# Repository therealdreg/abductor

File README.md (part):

# Abductor

The Abductor is an adapter board that lets you run CW312 targets on a ChipWhisperer CW308 UFO. The UFO
takes targets on three 20-pin 2.54 mm headers, and CW312 targets have a 1.00 mm card edge. The Abductor
has the UFO header footprint and a card-edge socket, and maps every UFO target signal to the CW312 edge.
Ten edge pins have no UFO counterpart and stay unconnected: TRACECLK and TRACED0-3, nRST_OUT, VCC1.0,
VCCADJ, CLKIN_n and CLKOUT_n. A CW312 target with the standard pinout should run on the UFO unless it
needs one of those. The name fits the UFO theme: the UFO abducts the CW312 target.

A dedicated target board built for one use case is usually the better choice. When that is not practical
or not possible, the Abductor is a low-cost alternative.

There are two variants. The straight board has a vertical socket on top and needs two small corners
trimmed off each CW312 target. The right-angle board has a right-angle socket on the underside, past the
end of the UFO headers, so no target needs trimming.

In my tests with three CW312 targets and a Husky Plus, both boards matched the target plugged directly
into a CW313 baseboard ("the CW313") on every chip and debug-port ID, known-answer test, key recovery and
fault outcome. Some single-run metrics were lower through the Abductor and some higher. SAM4S SNR was
11.5 dB through the Abductor and 12.2 dB on the CW313. K82F TVLA (a fixed-vs-random leakage t-test)
reached max |t| 100.6 on the straight board and 96.0 on the right-angle board, against 65.8 on the CW313,
whose capture was noisier.

Discussion and questions:
[NewAE forum thread](https://forum.newae.com/t/abductor-a-cw312-to-cw308-ufo-adapter-board/6514).

## Quick start

1. Order the boards from [prj/gerber.zip](prj/gerber.zip) (straight) or
   [prj/right_angle/gerber.zip](prj/right_angle/gerber.zip) (right-angle);
   [Ordering the PCB](#ordering-the-pcb) has the JLCPCB settings.
2. Solder one Samtec socket and three 20-pin male headers on each board
   ([Bill of materials](#bill-of-materials)).
3. For the straight board, trim two corners off each CW312 target
   ([Trimming targets for the straight board](#trimming-targets-for-the-straight-board)).
4. Plug the Abductor into the UFO and connect the Husky Plus: the 20-pin ribbon, and Measurement Pos to
   the UFO's J17 SMA, with Crowbar on a tee for glitching ([Cables](#cables)).
5. Set the UFO jumpers and switches, and add the J8 wires for SWD or JTAG
   ([UFO jumpers and switches](#ufo-jumpers-and-switches), [Debug wires on J8](#debug-wires-on-j8)).
6. Install the Python packages, change the hard-coded paths in the scripts and run them
   ([Running the scripts](#running-the-scripts)).

## Scope and limitations

All results come from one operator on one bench, with one unit of each Abductor variant, one
ChipWhisperer Husky Plus and one of each target (CW312T-SAM4S, CW312T-iCE40UP, CW312T-K82F), at
chipwhisperer commit `3c8e4347`. Most figures (SNR, TVLA t, |rho|, glitch bypass rates) come from a
single run, and unless repeats are reported I did not measure their run-to-run or re-assembly variance.
Words like "same" and "close" describe these sessions, not the hardware in general. Numbers with a plot
or an evidence file in `validation/` can be checked against it. The rest come from script console output
that is not in the repository, such as the K82F CPA, noise and mask figures, the glitch rates and the Lab
2_1B margins.

I am an enthusiast, not a professional hardware or side-channel engineer. The board and these notes may
contain mistakes or design choices a specialist would make differently. Read them as an informal
engineering log written in good faith, not as a datasheet or a qualified test report. After this testing
I consider the electrical design validated for my own use. Corrections and reviews are welcome.

## Building the board

### Ordering the PCB

Gerbers: [prj/gerber.zip](prj/gerber.zip) for the straight board and
[prj/right_angle/gerber.zip](prj/right_angle/gerber.zip) for the right-angle board. I do not work in
KiCad regularly, so review the sources and the gerbers before you order boards or rely on them.

The board carries many signals: power and shunt sensing, the HS2 clock (the ChipWhisperer high-speed
clock output), serial, the crowbar glitch path, the JTAG and SWD lines, the trigger, the LEDs and GPIO. I
chose six layers to route them comfortably. Every signal and rail runs as a 0.2 mm track on the four
inner layers. The two outer layers are ground pours, and ground fills the inner layers around the tracks.
At about 7 MHz the signal-integrity gain should be small, and my results show no consistent improvement
over a target plugged directly into the CW313. I never built a four-layer board, so I cannot say whether
it would perform the same.

The finish is ENIG. Both Samtec sockets are through-hole parts and the board has no gold-finger edge of
its own, so a cheaper HASL finish would most likely work too.

I ordered five of each variant from JLCPCB (https://jlcpcb.com/quote). It was a small, cheap order, and
the boards worked in all my tests. JLCPCB made them to this spec:

| JLCPCB parameter | Value |
|---|---|
| Base material | FR-4, TG135 |
| Layers | 6 |
| Dimensions | 54 mm × 67 mm (straight), 54 mm × 84.5 mm (right-angle) |
| Thickness | 1.6 mm |
| Outer / inner copper | 1 oz / 0.5 oz |
| Surface finish | ENIG, 1 µin gold (1U″) |
| Solder mask / silkscreen | Green / white, ink-jet |
| Via covering | Epoxy filled and capped |
| Min via | JLCPCB option: 0.3 mm hole, 0.4 to 0.45 mm diameter. The vias on both boards are 0.3 mm hole, 0.6 mm diameter |
| Electrical test | Flying-probe, full |
| Appearance quality | IPC Class 2 |
| Outline tolerance | ±0.2 mm |

### Bill of materials

| Part | Description | Link |
|---|---|---|
| Samtec PCIE-064-02-F-D-TH | Card-edge socket for the straight board: 1.00 mm pitch, 64 positions (the length of a PCIe x4 slot), through-hole | [Mouser](https://www.mouser.es/ProductDetail/Samtec/PCIE-064-02-F-D-TH?qs=iT52DjcXudu3X3%2FATBSy9g%3D%3D) |
| Samtec PCIE-064-02-F-D-RA | Right-angle version of the same socket, for the right-angle board | [Mouser](https://www.mouser.es/ProductDetail/Samtec/PCIE-064-02-F-D-RA?qs=92ilVni64gwDtfpZKan9%2FQ%3D%3D) |
| Preci-dip 800-10-020-10-001101 | Male header: 20-pin, 2.54 mm machined pin strip | [Mouser](https://www.mouser.es/ProductDetail/437-8001002010001101) |
| Preci-dip 801-87-020-10-001101 | Female socket strip: 20-pin, 2.54 mm machined, the header used on the CW308 itself. Not fitted on my boards; NewAE suggests it for sockets on its own CW308 to CW312 adapter | [Mouser](https://www.mouser.es/ProductDetail/437-8018702010001101) |

Each board takes one Samtec socket and three 20-pin male headers. The headers sit on the back of the
board, with their pins pointing down into the UFO. The PCB has no other parts: the Abductor only routes
signals.

NewAE's CW313 documentation only calls its socket the "cost-optimized CW312 card edge connector". The
CW313's Altium source in
[newaetech/chipwhisperer-target-cw313](https://github.com/newaetech/chipwhisperer-target-cw313) lists it
as a Samtec PCIE-064-02-S-D-RA. I picked the two Samtec sockets from the same PCIE series; NewAE does not
specify them. I use them only for their mechanical fit to the 1.00 mm card edge. Their PCIe signaling
rating does not matter here, since nothing on the edge comes near PCIe rates: DC rails, a clock of about
7 MHz, and slow serial, debug and GPIO lines.

### Trimming targets for the straight board

**On the straight board you have to trim two small corners off each CW312 target board**, one on each
side of the card edge. They hit the Abductor's header pins when the target is seated. The straight
board's vertical socket sits inside the UFO header frame, and the official ChipWhisperer target boards
are fixed products, so the design cannot avoid the corners. You trim each target once.

The photos show the trim on a CW312T-K82F target. The first marks the two corners. Nip each corner with
flush cutters, away from the target's mounting hole, then sand the edge, as the next two show.

This is roughly how much of the corner to remove:

### KiCad 10 sources

The KiCad projects are in [prj/](prj/) for the straight board and [prj/right_angle/](prj/right_angle/)
for the right-angle board. The schematic comes from NewAE's `CW308T_toCW312T` design in
[newaetech/chipwhisperer-target-cw308t](https://github.com/newaetech/chipwhisperer-target-cw308t/tree/main/CW308T_toCW312T),
an Altium schematic with no PCB layout or gerbers. That design is NewAE's "CW308 to CW312 Adapter", which
goes the other way: a CW308-style target solders onto it, and its card edge plugs into a CW312 baseboard
such as the CW313. NewAE ships it in the Husky Plus kit. I did the PCB layout in KiCad. The design uses
[ViaStitching](https://github.com/dobredanielstelian/ViaStitching), a KiCad 10 port of JS Reynaud's
via-stitching plugin (`jsreynaud/kicad-action-scripts`), and uPesy's easyeda2kicad
(`pip install easyeda2kicad`), whose output targets KiCad 6 and later. I imported the two socket
footprints with easyeda2kicad. The first command is for the straight board and the second for the
right-angle board:

```
python -m easyeda2kicad --full --lcsc_id=C4597619 --output "C:\\path\\to\\project" --project-relative --overwrite

python -m easyeda2kicad --full --lcsc_id=C4571870 --output "C:\\path\\to\\project\\right_angle" --project-relative --overwrite
```

LCSC `C4597619` is the Samtec PCIE-064-02-F-D-TH and `C4571870` the Samtec PCIE-064-02-F-D-RA. The
imported footprints, symbols and 3D models are already in each project folder (`easyeda2kicad.pretty`,
`easyeda2kicad.kicad_sym` and `easyeda2kicad.3dshapes`), so you need these commands only to import them
again.

The schematic names the two clock nets from the scope side. Its `/CLKOUT` net carries HS2 to card-edge
pin B27, the target's CLKIN, and its `/CLKIN` net carries the target's clock output from edge A29 to the
UFO.

### Pin map

UFO pins A, B and C are NewAE's target headers J7 (west), J9 (south) and J11 (east). CW312 pins A and B
are the two sides of the card edge. Both boards map the pins the same way.

| Signal | UFO pin | CW312 edge pin |
|---|---|---|
| VCC1.2 | C11 | B7 |
| VCC1.8 | C12 | B8 |
| VCC2.5 | C13 | A4 |
| VCC3.3 | C14 | A5 |
| VCC5.0 | C15 | A6 |
| FILTIN | C8 | B5 |
| FILT_HP | C6 | B4 |
| FILT_LP | C5 | A3 |
| SHUNTH | C3 | B2 |
| SHUNTL | C2 | B1 |
| IOVREF (the UFO's VREF) | A20 | B10 |
| Clock to the target (UFO CLK-IN, net `/CLKOUT`) | A3 | B27 |
| Clock from the target (UFO CLKOUT, net `/CLKIN`) | A5 | A29 |
| GPIO1/TX | A7 | B16 |
| GPIO2/RX | A8 | B17 |
| GPIO3 | A9 | B18 |
| GPIO4/TRIG | A10 | B19 |
| nRST | A11 | B14 |
| SCK | A12 | B20 |
| MISO | A13 | B23 |
| MOSI | A14 | B24 |
| PDIC | A17 | B25 |
| PDID | A18 | B26 |
| JTAG_TRST | B2 | A32 |
| JTAG_TDI | B3 | B29 |
| JTAG_TDO | B4 | B30 |
| JTAG_TMS | B5 | B31 |
| JTAG_TCK | B6 | B32 |
| JTAG_VREF | B7 | A26 |
| JTAG_nRST | B8 | A31 |
| LED1 | C18 | B11 |
| LED2 | C19 | B12 |
| LED3 | C20 | B13 |
| HDR1 to HDR10 | B11 to B20 | A9 to A18 |
| GND | A2, A4, A6, A15, A16, B1, B9, B10, C1, C4, C7, C9, C10, C16, C17 | A1, A2, A8, A20, A27, A28, B3, B9, B15, B21, B22 |
| TRACECLK, TRACED0 to TRACED3 | not connected | A21, A22 to A25 |
| nRST_OUT | not connected | A19 |
| VCC1.0 | not connected | B6 |
| VCCADJ | not connected | A7 |
| CLKIN_n, CLKOUT_n | not connected | A30, B28 |
| UFO spare pins | A1, A19 | not connected |

## Using the board

Plug the Abductor into the UFO target headers like any CW308 target, then plug the CW312 target into the
Abductor's socket. The Abductor has no jumpers or settings. To pull it off the UFO without stressing or
damaging the PCB I use a 3D-printed removal tool:
https://github.com/therealdreg/removal_tool_cw308_ufo_chipwhisperer

The software needs no change for the Abductor. The same scripts in `validation/scripts/` and the same
target builds ran on the CW313 and on both boards: `PLATFORM=CW312_SAM4S` for the SAM4S, the
`iCE40UP5K_SS2` bitstream for the iCE40 and `PLATFORM=CW308_K82F` for the K82F.

### Cables

The Husky Plus connects to the UFO with two cables, as in the photo:

- The 20-pin ribbon, from the Husky Plus "20-Pin Connector" to the UFO's 20-pin header J1. It carries the
  HS2 clock, serial on TIO1 and TIO2, the trigger on TIO4, nRST, PDIC, the SPI lines and the 3.3 V that
  powers the UFO. NewAE rates that 3.3 V at 200 mA, and the 20-pin 5 V pin is connected only on a CW-Pro,
  so the UFO runs on 3.3 V alone.
- An SMA cable from "Measurement Pos" to J17, the UFO's only SMA (silkscreen VOUT). Its center pin is
  SHUNTL, the low side of the shunt resistor on the CW312 target. For voltage glitching, put an SMA tee
  on J17 and run a second cable from "Crowbar" to it. The tee that came with the UFO works;
  [Bypass rate by tee and setup](#bypass-rate-by-tee-and-setup) compares it with an Amphenol 132217.

"Measurement Neg", "Trig/Glitch" and "Aux" stay unused. For single-ended measurement NewAE recommends
fitting the short-circuit cap that ships with the Husky on Measurement Neg, which makes the trace
slightly less noisy; my bench ran without it. On the CW313 the two SMAs are wired together, so Crowbar
and Measurement Pos take one each and need no tee.

### UFO jumpers and switches

These settings run all three targets from the Husky Plus alone, with nothing on the UFO's DC jack. The
bench photos show the J3, J4 and J14 caps fitted and J16 open, but the regulator switches are too small
to read in them, so the switch settings below follow from what the targets need.

| Jumper or switch | Setting | Why |
|---|---|---|
| J3, clock | HS2/OUT to CLKIN, the NewAE default | sends the Husky Plus HS2 clock to the target CLKIN. The other positions take the X1 crystal or send CLKFB, the target's clock output, to the ChipWhisperer |
| 3.3V SRC switch | J1/CW | takes 3.3 V straight from the 20-pin cable. The LDO position needs a DC supply or the CW-Pro 5 V |
| 1.2V LDO SRC switch | J1 | feeds the 1.2 V LDO from the ChipWhisperer 3.3 V. The SAM4S and the iCE40 take their 1.2 V core supply from it; the K82F (revision -03, the board used here) runs on 3.3 V only |
| J14, filter input | FILT, the NewAE default | the target feeds its core supply into the UFO filter through FILTIN (CW312 edge B5). The VADJ position feeds the filter from the adjustable LDO instead: set its voltage first, because the SAM4S and iCE40 cores run at 1.2 V |
| J16, shunt | open | a cap across SH- and SH+ shorts the shunt and removes the power signal. A cap across GND and SH- shorts the target supply to ground through the shunt: on the K82F that is about 330 mA from the Husky Plus 3.3 V, which is rated at 200 mA |
| J4, VREF | J5-VREF (the NewAE default) or CW 3.3 V | sets the clamp level of the 20-pin I/O lines. J5-VREF takes it from the target's VREF pin, which the Abductor carries to CW312 edge B10 (IOVREF), and all three targets drive that pin at 3.3 V. CW 3.3 V sets the same 3.3 V from the 20-pin cable. The close-ups with the K82F appear to show the cap on the CW 3.3 V side |
| EXT-DC switch | either | matters only with a DC supply on the jack |

These targets use none of the other supplies, so the 1.8V, 2.5V and 3.3V LDO SRC switches, the 5V SRC
switch, the VADJ SRC switch and the VADJ trimmer can stay as they are.

On the CW313, JP2 stays on target GPIO4 (the default) for the trigger, and the JP3 caps make the debug
bridge described in [SWD and JTAG debug](#swd-and-jtag-debug).

### Debug wires on J8

The UFO has no JP3 jumpers like the CW313's, so SWD and JTAG on the SAM4S, and flashing the K82F, need
jumper wires on the UFO from J5, the pin header next to J4 that carries the target connector's
ChipWhisperer signals, to the JTAG pins of J8. J8 is printed, from the left: GND, J_TRST, J_TDI, J_TDO,
J_TMS, J_TCK, J_VREF, nRST, GND, GND, then H1 to H10. The silkscreen font draws a V like a U, so J_VREF
can read as J_UREF (and VREF on J5 as UREF). Ground is already common through the 20-pin ribbon. SWD
needs wires 1 to 3, and full JTAG adds 5 and 6:

| Wire | From | To (J8) | Role |
|---|---|---|---|
| 1 | `SCK` | `J_TCK` | SWCLK |
| 2 | `PDID/CS` | `J_TMS` | SWDIO |
| 3 | `VREF` | `J_VREF` | JTAG_VREF for the pull-ups |
| 4 | `nRST` | `J_TRST` (SWD, K82F) or `nRST` (JTAG) | optional; OpenOCD drives no reset |
| 5 | `MOSI` | `J_TDI` | TDI, full JTAG only |
| 6 | `MISO` | `J_TDO` | TDO, full JTAG only |

SWD needs wire 3: without it OpenOCD failed with `cannot read IDR` in my setup. Wire 4 is optional, and
the logs show it on two different pins. The SWD and K82F sessions ran it to J_TRST, which reaches JTAG
TRST at CW312 edge A32 (unconnected on the SAM4S and the iCE40, PTA5/TRST on the K82F). The JTAG session
ran it to J8's nRST, which reaches edge A31 (JTAG_nRST, which the SAM4S ties to its nRST). OpenOCD drove
no reset line in any session. Take all these wires off before you use the iCE40. They tie `nRST`, `VREF`
and the SPI lines to the `J8` JTAG pins, and in my tests the iCE40's SS2 serial only worked without them.

## Validation

I tested the board on ChipWhisperer hardware one demo at a time, in the course order starting with
`sca101`, and checked each result before moving on. The tests check that the Abductor carries the signals
each demo needs and gives valid side-channel data.

The tests ran on three setups with the same targets and Husky Plus: the straight board, the right-angle
board, and the CW313, where the target plugs directly into the CW313 baseboard with no UFO and no
adapter. Results are from the straight board unless a section says otherwise. In file names and script
labels, `abductor` means the straight board.

The right-angle board's socket is a right-angle part, so its traces are a little longer and routed
differently. That could add series inductance and loop area on the crowbar/VOUT and shunt paths, or
slightly reduce the measurement bandwidth. I re-ran all three targets through it with the same Husky
Plus, UFO and scripts, one test at a time, and reconnected the Husky Plus USB between tests. A test that
failed on the first attempt was re-run after a USB reconnect.

### Results

In the verdict column, identical means a bit-exact match of a fixed value (IDs, known-answer tests). Same
means the same outcome or count. Close means a difference these runs cannot resolve, so a small effect is
neither shown nor ruled out. Glitch points are (width, offset, ext_offset): width and offset are in Husky
phase-shift steps, and ext_offset is in target clock cycles after the trigger.

| Test | Metric | Straight | Right-angle | CW313 | Verdict |
|---|---|---|---|---|---|
| Bring-up | traces, serial echoes | 10/10, 10/10 | 10/10, 10/10 | 10/10, 10/10 | same |
| Bring-up | mean trace peak-to-peak (normalized ADC units) | 0.57 | 0.68 | 0.62 | within 19%, one run each |
| CPA (AES) | full key | yes | yes | yes | same |
| CPA | traces to rank 0 (all 16 key bytes ranked first) | 30 | 30 | 30 | same |
| DPA (AES) | full 16-byte key | yes | yes | yes | same |
| Password SPA | recovered | `h0px3` | `h0px3` | `h0px3` | same |
| Password SPA | winner margin | 22x to 24x | 23x to 25x | 23x to 24x | close |
| SNR | peak, 1500 traces | 14.1 (11.5 dB) | 14.0 (11.5 dB) | 16.7 (12.2 dB) | CW313 18% higher (linear) |
| TVLA | max \|t\| (3000 traces, threshold 4.5) | 60.7 | 59.5 | 60.7 | close |
| GPIO3 | TIO3 toggles | yes | yes | yes | same |
| SWD | DPIDR, chip ID | `0x2ba01477`, `0x288b07e1` | `0x2ba01477`, `0x288b07e1` | `0x2ba01477`, `0x288b07e1` | identical |
| JTAG | TAP IDCODE | `0x4ba00477` | `0x4ba00477` | `0x4ba00477` | identical |
| Voltage glitch, high-power | best cell found (width, offset, ext_offset) | (1950, 2480, 129) | (2000, 2450, 129) | (1950, 2460, 129) | same ext_offset, offsets 2450 to 2480 |
| Voltage glitch, high-power | batch bypass rate (200 attempts) | 49.5% | not measured | 40.5% | gap not resolved (p about 0.07) |
| Voltage glitch, high-power | peak bypass rate (40 attempts at the best cell) | 78% and 98% (Amphenol tee), 55% (stock tee) | 90% (36/40) | 85% (34/40) | bypasses on all three; single runs do not rank them |
| Voltage glitch, low-power | crashes at repeat 1, 2, 4, 8 | none at 1, all at 2 to 8 | none at 1, all at 2 to 8 | none at 1, all at 2 to 8 | same threshold |
| Clock glitch | faults the SAM4S | yes | yes | yes | same |
| LED1, LED2, LED3 | blink in sequence | yes | yes | yes | same |
| Memory dump | crowbar on the send loop | 510 bytes at (2000, 2480, 2122), no secret | 510 bytes at (1900, 2200, 88), contains the secret | 510 bytes at (2000, 2480, 2122) | same fault and length; the right-angle glitch point differs |
| iCE40 AES | known answer `AES(0,0)` | `66e94bd4...` | `66e94bd4...` | `66e94bd4...` | identical |
| iCE40 CPA | traces to full key (grid ..., 2000, 3000) | 3000 | 3000 (repeat; first run 5000) | 3000 | same |
| iCE40 TVLA | max \|t\| (4000 traces, threshold 4.5) | 85.0 | 85.8 | 89.3 | within 5% |
| iCE40 DFA (differential fault attack) | full key (phoenixAES, round-8 and round-9 faults) | 16/16 | 16/16 | 16/16 | same |
| K82F AES | known answer `AES(2b7e..,00..0f)` | `50fe67cc...` | `50fe67cc...` | `50fe67cc...` | identical |
| K82F TVLA | max \|t\| (8000 traces, threshold 4.5) | 100.6 | 96.0 | 65.8 | all far above 4.5, wide spread |
| K82F CPA | byte-0 \|rho\| (50k traces; right-angle 30k) | 0.104 | 0.104 | 0.095 | close (standard error about 0.005 each) |
| K82F CPA | full AES key, disjoint-set attack | not recovered (1/16 at 50k, 0/16 at 30k) | not recovered (0/16 at 30k) | not recovered (0/16) | same; the limit is the target (one control run) |

Traces to rank 0 is a single-run count on a coarse trace grid. It depends on the data, can change from
run to run, and is not a guessing-entropy average (the mean rank of the correct key over many runs).

## CW312T-SAM4S

### Bring-up

All six steps of a smoke test passed, so the Abductor routes clock, power, serial, ERASE and nRST, and
the chain from the Husky Plus through the UFO and the Abductor to the SAM4S works. The test builds
`simpleserial-base`, flashes it over SAM-BA and captures traces. Steps 2 to 5 each exercise a different
path through the Abductor. Script: [`smoke_bringup.py`](validation/scripts/smoke_bringup.py).

| # | Step | Abductor path | Result |
|---|---|---|---|
| 0 | Connect to the Husky Plus | none (scope only) | `cwhuskyplus`, FW 1.2.0 |
| 1 | Build the SAM4S firmware | none (host build) | `simpleserial-base-CW312_SAM4S.hex`, ROM 2.17% of 128 KB |
| 2 | Flash over SAM-BA (ERASE=`pdic`, `nrst`) | control and reset lines | program and verify OK in 5.0 s |
| 3 | Bidirectional UART, echo of the `p` command | serial TX and RX | 10/10 echoes correct |
| 4 | Trigger and capture | trigger and sync | 10/10 traces, 5000 samples each |
| 5 | Clock and power measurement | HS2 clock, shunt and SMA | mean per-trace peak-to-peak 0.57 and global sample std 0.14 (normalized ADC units), clean clock cycles |

### Side channel (sca101)

Every lab I ran passed. The `sca101` course builds up from timing differences to a full AES key recovery.
I skipped Lab 3_2, which is software only, and Lab 4_1, a low-impact stepping stone. Labs 4_3, 5_1 and
6_4 are pending.

| Lab | Title | Firmware | Result |
|---|---|---|---|
| 2_1A | Instruction power differences | simpleserial-base | pass |
| 2_1B | Power analysis for password bypass | basic-passwdcheck | pass |
| 3_1 | Large Hamming weight swings | simpleserial-aes (TINYAES128C) | pass |
| 3_2 | Recovering data from a single bit | none | skipped (software only) |
| 3_3 | DPA on firmware implementation of AES | simpleserial-aes (TINYAES128C) | pass, full key |
| 4_1 | Power and Hamming weight relationship | simpleserial-aes | skipped |
| 4_2 | CPA on firmware implementation of AES | simpleserial-aes (TINYAES128C) | pass, full key in 30 traces |
| 4_3 | ChipWhisperer Analyzer CPA attack | simpleserial-aes | pending |
| 5_1 | ChipWhisperer CPA attacks in practice | simpleserial-aes | pending |
| 6_4 | Jittery triggering on UART | simpleserial-aes (TINYAES128C) | pending |

#### Lab 2_1A: instruction power differences

I inserted different instruction blocks between `trigger_high()` and `trigger_low()` in
`simpleserial-base`, then built (ChipWhisperer's default `-Os`), flashed and captured each one. As the
lab instructs, I removed the serial response (`simpleserial_put`) from `get_pt()`, so no reply follows
the block. The framework still sends its `z00` ack. `capture_trace` reads it in place of the missing `r`
packet, warns `Unexpected start to command` and keeps the trace. Serial stays in sync because
`simpleserial_write` flushes the receive buffer before each command. Script:
[`lab_2_1A.py`](validation/scripts/lab_2_1A.py).

The cost of each block is the trigger duration, `scope.adc.trig_count`. That counter counts ADC samples:
at `adc_mul=4` there are 4 samples per core clock cycle, so the counts are 4 times the core cycles.

| Instruction block | Trigger duration (ADC samples) | Cost against baseline |
|---|---|---|
| baseline (empty) | 492 | reference |
| 20x `A *= 2` (unrolled multiply) | 992 | +500, 25 ADC samples (6.25 core cycles) per volatile statement |
| loop x20 `A *= 2` (multiply) | 2132 | +1640, 82 ADC samples (20.5 core cycles) per iteration |
| loop x20 `A /= 3` (integer divide) | 2276 | +1784, 144 more than the multiply loop |

- The count was identical in all 15 captures of each block (min equals max), as expected from
  deterministic code clocked in step with the ADC. That is consistent with the count coming back through
  the Abductor uncorrupted. The right-angle board gave the same four counts.
- The unrolled block adds a flat cost per statement. The loop costs far more than the same 20 multiplies
  unrolled. That extra fits per-iteration loop overhead (the volatile counter load and store, compare and
  branch), but the measurement only records the total.
- The divide loop costs more than the multiply loop. `A` is a `volatile long int`, so `A /= 3` is integer
  division. The compiler can emit the multi-cycle Cortex-M4 `SDIV` or, for a constant divisor like 3, a
  multiply-and-shift sequence, and the repository has no listing to tell which. The trigger duration
  cannot tell the two apart either, so it does not prove an `SDIV` ran.

Both figures label the counts as cycles and draw the block end at four times the count. The counts are
ADC samples, so the blocks end at samples 492, 992, 2132 and 2276, and `lab_2_1A.py` labels and draws
them that way.

#### Lab 2_1B: power analysis for password bypass

The power traces recover the password of `basic-passwdcheck`, `h0px3`, which matches the firmware
constant. The correct character wins every position by 22x to 24x. The firmware checks the password one
character at a time and stops at the first wrong one. Each correct character runs one more loop
iteration, so the trace stays active longer before it diverges. The attack captures one trace per
candidate character, scores it against a wrong-character reference with the sum of absolute differences
(SAD), keeps the best score, and moves to the next position with the known prefix. Script:
[`lab_2_1B.py`](validation/scripts/lab_2_1B.py).

| Position | Recovered char | SAD (winner) | SAD (2nd best) | Margin |
|---|---|---|---|---|
| 0 | `h` | 286.6 | 11.9 | 24.0x |
| 1 | `0` | 284.6 | 12.4 | 22.9x |
| 2 | `p` | 280.3 | 12.7 | 22.1x |
| 3 | `x` | 274.5 | 12.4 | 22.1x |
| 4 | `3` | 301.7 | 12.3 | 24.4x |

Margins come from the full-precision SAD values, so they can differ slightly from dividing the rounded
columns. In the divergence plot the correct and wrong first-character traces overlap until the compared
byte and split around sample 430.

#### Lab 3_1: large Hamming weight swings

The target's power depends on the data it handles as well as on the code path. With `simpleserial-aes`
(TINYAES128C) and a fixed key, I captured 200 traces with plaintext byte 0 forced to `0x00` (Hamming
weight 0) or `0xFF` (Hamming weight 8). Bit 0 of the original random byte picks the value (odd gives
`0xFF`, even gives `0x00`), which splits the traces about evenly. The difference of the two group means
is the data-dependent leak. Script: [`lab_3_1.py`](validation/scripts/lab_3_1.py).

| Metric | Value |
|---|---|
| Traces | 200, about 100 at `0x00` and 100 at `0xFF` |
| Peak difference | 0.0254 in magnitude at sample 528 (negative) |
| Off-peak std (difference trace beyond ±400 samples from the peak) | 0.0008 |
| Leak-to-noise ratio | peak about 32x the off-peak std (an informal single-run ratio, not an SNR) |

A sharp negative spike at sample 528, where the target loads and processes that byte, dominates the
difference of means. The spike is negative because ChipWhisperer measures across a shunt: more power
reads as lower voltage, and `0xFF` (more bits set) draws more power than `0x00`. A smaller positive
spike, about +0.013 near sample 1930, lines up with the S-box output of the same byte. The Lab 3_3 DPA
peak sits at the same sample. The sign fits too, because `SBox(0xFF XOR 0x2b) = 0x48` has fewer bits set
than `SBox(0x00 XOR 0x2b) = 0xf1`. CPA on AES exploits that S-box leak, `HW(SBox(pt XOR key))`.

On the right-angle board the leak sits at the same sample 528, with a peak difference of 0.019 and a
leak-to-noise ratio of about 27x.

#### Lab 3_3: DPA on firmware implementation of AES

Single-bit DPA recovers the known key, `2b7e151628aed2a6abf7158809cf4f3c`, in all 16 bytes. This is the
first full key recovery in the suite. With `simpleserial-aes` (TINYAES128C) and a fixed key, I captured
2500 traces with random plaintexts, at about 119 traces/s. For each key byte and each of the 256 guesses,
the script splits the traces by bit 0 of `SBox(plaintext_byte XOR key_guess)` and subtracts the two group
means. The guess with the highest peak is the key byte. Script:
[`lab_3_3.py`](validation/scripts/lab_3_3.py).

For every byte the correct guess peaks above the best wrong guess. For byte 0 the correct guess `0x2b`
peaks sharply near sample 1930, at about 0.0033. The strongest wrong guesses reach about 0.0025 (`0x99`,
elsewhere in the trace) and about 0.002 (`0x40`, a ghost peak at the same sample). The margin is modest
because single-bit DPA is noisier than CPA.

#### Lab 4_2: CPA on firmware implementation of AES

Correlation power analysis (CPA) recovers the same key, all 16 bytes, from the first 30 traces on all
three setups. It is the stronger attack here, since it is less noisy than single-bit DPA. The model is
`HW(SBox(plaintext_byte XOR key_guess))`, and for each key byte the guess whose model has the highest
absolute Pearson correlation with the traces (max |rho| over the samples) is the key byte. Script:
[`lab_4_2.py`](validation/scripts/lab_4_2.py).

- 1000 traces captured, at about 120 traces/s.
- The correct byte reaches |rho| 0.91 to 0.94 and the best wrong guess 0.20 to 0.31, so the correct byte
  leads by 0.6 to 0.7. The correct byte reaches 0.87 to 0.90 on the right-angle board and 0.89 to 0.91 on
  the CW313.
- 30 traces is the first point on the trace grid (..., 20, 30, 40, ...) where all 16 key bytes reach rank
  0.

### SNR and TVLA

Two standard leakage metrics show how cleanly each path captures the AES leak. Script:
[`signal_integrity.py`](validation/scripts/signal_integrity.py), with a 3000-sample window on
`simpleserial-aes`. I ran it on all three setups at the same trace counts, so that only the path differs.

| Path | SNR peak, linear (dB) | TVLA max \|t\| |
|---|---|---|
| Straight board | 14.1 (11.5 dB) | 60.7 |
| Right-angle board | 14.0 (11.5 dB) | 59.5 |
| CW313 | 16.7 (12.2 dB) | 60.7 |

- SNR is `calculate_snr` from `chipwhisperer.analyzer`, with the Hamming weight of the S-box (SubBytes)
  output for byte 0 over 1500 random-plaintext traces, at the leak sample. ChipWhisperer's
  `calculate_snr(db=True)` returns `20*np.log(snr)`, and `numpy.log` is the natural log, so it reports
  `20*ln(snr)`, which is not standard dB. The dB values here are `10*log10` of the linear SNR (see
  `software/chipwhisperer/analyzer/attacks/snr.py`).
- TVLA is a non-specific fixed-vs-random Welch t-test, the leakage-detection method of Goodwill, Jun,
  Jaffe and Rohatgi (2011), later branded TVLA. It runs over about 1500 fixed and 1500 random traces
  (3000 total, split by a coin flip per trace), and the usual detection threshold is 4.5. A raw t value
  also grows with the trace count, so it is only a relative measure at matched counts.

The exact TVLA match between the straight board and the CW313, to three significant figures from two
independent trace sets, is chance and will not repeat to that precision. SNR is about 0.7 dB higher on
the CW313. With one estimate per path there is no spread to test that against, so a small real loss
through the Abductor is neither shown nor ruled out. The same holds for the somewhat smaller Lab 3_1 and
Lab 4_2 leaks on the right-angle board. Settling it would need repeated captures on each path.

SNR and TVLA come from the ChipWhisperer capture path, not from a direct bench measurement of the board.
I may later probe both boards directly with my MHO98 and an LD-ASP-2.7 single-ended active probe.

### Fault injection (fault101)

The glitch tests used the SMA tee from [Using the board](#using-the-board), stock UFO jumpers and the
stock SMA cables that ship with the Husky Plus and the CW313. The Husky Plus has a high-power and a
low-power crowbar MOSFET, and each one briefly shorts the target supply. This exercises the Abductor's
crowbar path, a different use of the power pins from power measurement.

#### Fault 2_2: voltage glitching to bypass password

`simpleserial-glitch` checks a fixed password (`touch`). A wrong password (`[0]*5`) normally returns
`passok=0`. A high-power crowbar glitch during the compare loop can leave `passok=1`, so the firmware
accepts the wrong password. That is a bypass. I used `scope.vglitch_setup('hp')`, with
`scope.io.vglitch_reset()` after each attempt, and swept widths 1900 to 2200, offsets 2380 to 2500 and
ext_offset 122 to 140, twice each: 2964 attempts. Bypasses appeared only at ext_offset 129, on both
boards:

| Board | Bypasses | Offsets | Widths |
|---|---|---|---|
| Straight | 12 in 2964 | 2460 to 2500 | 1900 to 2140 |
| Right-angle | 15 in 2964 | 2430 to 2500 | 1960 to 2200 |

Both windows reach the edge of the swept grid, so they may extend further. On the straight board the 12
bypasses are 0.4% of the whole grid, and 20% of the 60 attempts at offsets 2460 to 2500 and ext_offset
129 over all six widths. The window is a single ext_offset value, so a sweep with a coarse ext_offset
step misses it. [`fault_2_2_vglitch_find.py`](validation/scripts/fault_2_2_vglitch_find.py) finds the
first bypass with a sweep that is coarse in width and offset but steps ext_offset by 1, and
[`fault_2_2_vglitch_bypass.py`](validation/scripts/fault_2_2_vglitch_bypass.py) maps the window. The
shared VOUT tee and the SMA cabling may also narrow the window; I did not measure that.

#### Bypass rate by tee and setup

In these tests the Abductor carried voltage glitching with either tee. I measure the peak bypass rate at
each setup's best cell: a fine search finds the cell, then 40 attempts run there. The best cell is the
best on the swept grid, not a verified global optimum.
[`vglitch_peakrate.py`](validation/scripts/vglitch_peakrate.py) runs this on a fixed grid (widths 1800 to
2200, offsets 2360 to 2520, ext_offset 128 to 130) and warns when the best cell sits on a width or offset
edge, where the rate comes out low.

| Setup | VOUT tee | Peak bypass rate |
|---|---|---|
| Straight board, back to back on one fresh re-assembly | Amphenol 132217 (low-cost SMA jack-plug-jack T, Mouser 523-132217) | 31/40 = 78% |
| Straight board, the same re-assembly | the tee that came with the UFO | 22/40 = 55% |
| Straight board, another re-assembly | Amphenol 132217 | 39/40 = 98% |
| CW313 | none (two dedicated SMAs) | 34/40 = 85% |

The right-angle board gave 36/40 = 90% at its best cell (95% CI about 76% to 97%), which overlaps the
straight board's 78% to 98% with the Amphenol tee.

The batch rate over 200 attempts (five 40-attempt batches,
[`vglitch_rate_robust.py`](validation/scripts/vglitch_rate_robust.py)) at each setup's best cell, found
the same day, is 49.5% through the straight board and 40.5% on the CW313. The 9-point gap is about 1.8
standard errors (standard error of the difference about 5 points, two-sided p about 0.07), so 200
attempts per setup cannot resolve it. These batch rates sit below the 40-attempt peaks:
`vglitch_rate_robust.py` picks its cell with a coarser search (2 attempts per cell, offset step 20), and
the peaks came from other assemblies.

With the Amphenol tee the Abductor is not measurably worse than the CW313: 31/40 and 39/40 against 34/40,
two-sided Fisher exact p 0.57 and 0.11. The stock-tee run (22/40) is lower than the CW313's 34/40 (p
about 0.007), but I measured them on different assemblies, and re-assembly moved the Amphenol rate from
31/40 to 39/40 (p about 0.014). So these single runs do not rank the setups.

The Amphenol tee may help, but that is not established. A two-sided Fisher exact test on the back-to-back
counts (31/40 against 22/40) gives p about 0.06, above the 0.05 level, so one pair of 40-attempt runs
cannot settle it. The 22.5-point gap is about the size of the 20-point spread between the two Amphenol
re-assemblies. Pinning down a modest tee effect would take repeated swap-and-measure runs.

#### Low-power crowbar

[`fault_2_2_vglitch_lp.py`](validation/scripts/fault_2_2_vglitch_lp.py) uses the low-power crowbar
(`scope.vglitch_setup('lp')`) at width 2000, offsets 2440 to 2470 and ext_offset 126 to 136, and sweeps
`scope.glitch.repeat` over 1, 2, 4 and 8, with 18 attempts each. At repeat 1 there were no crashes (0 of
18, too few to rule out a low rate). At repeat 2, 4 and 8 the crowbar crashed the SAM4S on every attempt.
The sharp threshold indicates that the crashes follow the glitch setting instead of happening at random.
The right-angle board and the CW313 showed the same threshold. Both crowbars drive the same CROWBAR SMA,
so this test exercises the same SMA and VOUT path as the high-power one, not the `FILT_LP` pin.

#### Fault 2_3: voltage glitching to memory dump

`bootloader-glitch` answers a command with an 8-byte ack, sending exactly `ascii_idx` bytes with
`for(i=0; i<ascii_idx; i++) putch(ascii_buffer[i])`. A crowbar glitch on that loop bound makes the target
keep sending past the ack and dump the adjacent buffer and RAM, which can include the decrypted
`data_buffer`. Script: [`fault_2_3_memory_dump.py`](validation/scripts/fault_2_3_memory_dump.py), with
[`fault_2_3_baseline.py`](validation/scripts/fault_2_3_baseline.py) to confirm the protocol and measure
the send-loop `trig_count`. Both scripts sample at one ADC sample per target clock, so `trig_count` and
ext_offset are both in target clock cycles.

- The glitch is a high-power crowbar pulse at width 2000, offset 2480 and ext_offset 2122, inside the
  send loop (`trig_count` 2159). It lands 37 cycles before the loop ends, near the final bound check.
- The 8-byte ack became a 510-byte dump with the leftover input buffer and a block of binary RAM. The
  success marker `767` that the attack looks for is at offset 0x2a, inside the leftover input, which is
  the encrypted command text. So the marker shows an overrun, and this dump does not contain the
  decrypted secret.
- The hexdump in [`fault_2_3_memory_dump.txt`](validation/evidence/fault_2_3_memory_dump.txt) shows 601
  bytes because the printed text was saved as UTF-8: each byte from 0xa1 to 0xff except 0xad takes two
  bytes there (91 `c2`/`c3` pairs).
- Success is rare. The first one came after about 2100 swept attempts. That is the position of one
  success in an ordered parameter sweep, not a per-attempt hit rate, so take it as an order of magnitude.
  The glitch has to break the loop bound in a narrow window.
- All three dumps are 510 bytes. The CW313's came at the same glitch point, with its first success also
  near 2100 swept attempts. The right-angle board's came at (1900, 2200, 88), much later in the sweep, at
  attempt 13049. That fits a rare fault with several valid glitch points, and shows that an early glitch
  can work too. It is the only dump in the repository that contains the decrypted secret,
  `Don't forget to buy milk!`
  ([`fault_2_3_memory_dump_ra.txt`](validation/evidence/fault_2_3_memory_dump_ra.txt)).

#### Fault 1_2: clock glitching to bypass password

In ChipWhisperer's stock configuration the CW312T-SAM4S core runs directly on the external HS2 clock. The
SAM4S HAL switches the master clock to MAINCK in bypass mode (about 7.37 MHz, prescaler 1) and keeps the
PLLA out of the core path: `firmware/mcu/hal/sam4s/sam4s_hal.c` calls `osc_enable(OSC_MAINCK_BYPASS)` and
then `pmc_switch_mck_to_mainck(SYSCLK_PRES_1)`. So a glitch on HS2 reaches the core clock tree (MCK/HCLK)
with no PLL to regenerate the clock. The capture clock runs in step with the 7.363636 MHz HS2 clock,
which agrees with this but does not by itself rule out a PLL. The proof is the HAL source, and the fact
that clock glitches fault the core.

On PLL-clocked systems the PLL strongly attenuates a single external clock glitch, so a naive
single-cycle glitch usually fails. Faults there come from disturbing the PLL itself, for example driving
it into a transient frequency overshoot by manipulating its reference clock. See Selmke, Hauschild and
Obermaier, "Peak Clock: Fault Injection into PLL-Based Systems via Clock Manipulation", ASHES@CCS 2019,
Fraunhofer AISEC / ACM, DOI 10.1145/3338508.3359577.

On the CW313 I swept at repeat 1 only: widths 3350 to 3600, six offsets from 2300 to 2900 and ext_offset
85 to 158, about 5300 attempts. The clock glitch crashes the SAM4S, more often as the width grows. One
clean bypass appeared at the crash onset, at (3450, 2300, 142). It was a single event, so it gives no
success rate. On the map at width 3450, every crash and the bypass sit at offset 2300, the lowest offset
swept, spread across ext_offset 88 to 157; offsets 2400 to 2900 show nothing.

Through the straight board, a sweep over widths 3400 to 4500, offsets 2300 to 2900 and ext_offset 85 to
157 faults the SAM4S too. It runs 400 attempts at each value of `scope.glitch.repeat`, the number of
consecutive glitched cycles:

| Repeat | 1 | 2 | 4 | 8 | 16 | 32 |
|---|---|---|---|---|---|---|
| Crash rate | 2% | 15% | 20% | 30% | 34% | 42% |
| Clean bypasses | 0 | 0 | 1 | 1 | 1 | 0 |

The right-angle board showed the same pattern: the crash rate rose from about 2% at repeat 1 to about 40%
at repeat 32, with some clean bypasses. A higher repeat raises the crash rate; three clean bypasses are
too few to show whether it also raises the clean-fault rate.

A sweep that misses the reactive offsets or widths sees no effect at all, which looks like the path is
attenuating the glitch. At repeat 1 the straight board gave no clean bypass in 400 attempts and the CW313
gave one in about 5300, which does not separate the two paths. These single, unmatched runs cannot show
whether the path makes any difference; that would need matched sweeps on both setups.

Scripts: [`clock_glitch_cw313_bypass.py`](validation/scripts/clock_glitch_cw313_bypass.py) for the CW313
and [`clock_glitch_abductor_repeat.py`](validation/scripts/clock_glitch_abductor_repeat.py) for the
repeat sweep. The repeat sweep script prints its counts; no script in the repository draws the repeat
figure. [`clock_glitch_characterize.py`](validation/scripts/clock_glitch_characterize.py) maps glitch
width to effect, and
[`clock_glitch_cw313_isolation.py`](validation/scripts/clock_glitch_cw313_isolation.py) sweeps width,
offset and ext_offset on the CW313 to check whether the SAM4S rejects clock glitches.

### SWD and JTAG debug

SWD and full JTAG both work through the Abductor. The SAM4S gives the same DPIDR, core revision, TAP
IDCODE and chip ID through both boards as on the CW313. So the Abductor carries all four JTAG signal
lines: the data lines TDI and TDO and the control lines TMS and TCK. `JTAG_nRST`, `JTAG_TRST` and
`JTAG_VREF` were not exercised.

With the Husky Plus in MPSSE mode (its FTDI emulation) and OpenOCD, I took over the SAM4S via SWD: reset
and halt at the reset vector, then read the chip ID, SRAM, flash and core registers. The Husky Plus
drives SWD in non-DIO mode (`scope.enable_MPSSE(1)`), which puts the debug signals on the main 20-pin
SPI/PDI pins: PDID is SWDIO and SCK is SWCLK, the same mapping the non-Husky ChipWhisperer boards use.
OpenOCD then connects with `transport select swd` and the `at91sam4sXX` target config. In MPSSE mode the
USB PID stays `0xace6`, and the interface config is the stock ChipWhisperer `openocd/cw_openocd.cfg`.
Scripts: [`swd_debug.sh`](validation/scripts/swd_debug.sh) and
[`jtag_debug.sh`](validation/scripts/jtag_debug.sh).

I verified the flow on the CW313 first, to check the target and the toolchain. There the JP3 caps make
the bridge, so no external wiring is needed: `PDID` to `JTAG_TMS`, `SCK` to `JTAG_TCK`, `MOSI` to
`JTAG_TDI`, `MISO` to `JTAG_TDO`, `nRST` to `JTAG_nRST` and `PDIC` to `JTAG_TRST`. SWD needs the first
two, full JTAG the first four. Through the Abductor the bridge is the `J8` wires listed in
[Using the board](#using-the-board). From `J8` the debug lines reach the CPU through the UFO target
socket, the Abductor and the CW312 card edge.

The schematics do not explain why SWD needs the `VREF` wire. The UFO does not drive `JTAG_VREF` itself;
it only feeds the 100k pull-ups on the JTAG lines. The CW312T-SAM4S ties card-edge pin A26 (`JTAG_VREF`)
to its VCC, and the Abductor routes A26 to the UFO's `JTAG_VREF`. On the CW313, `JTAG_VREF` also comes
only from A26. The wire feeds the same net as the A26 route, so these sessions cannot tell the two apart.

OpenOCD drove no reset line. The raw CW313 logs print `none separate`, the reset configuration that
`cw_openocd.cfg` leaves (`reset_config srst_push_pull`), and the at91sam4 target config resets the core
with `cortex_m reset_config sysresetreq`. The same scripts and configs ran through the Abductor, so wire
4 was not exercised there either. `J_TRST` also lands, through the Abductor, on card-edge pin A32, which
the CW312T-SAM4S leaves unconnected.

The SWD readout through the straight board:

| Read over SWD | Value | Meaning |
|---|---|---|
| SWD DPIDR | `0x2ba01477` | ARM CoreSight SW-DP (DPv1) alive. This DPIDR is common on Cortex-M4 parts and later Cortex-M3 revisions, and identifies the debug port, not the core |
| Core | `Cortex-M4 r0p1` | SAM4S core, from CPUID |
| State | `halted due to debug-request` | the debugger halted the core straight out of reset, at the reset vector |
| CHIPID_CIDR @0x400E0740 | `0x288b07e1` | chip ID read from silicon, which decodes to ATSAM4S2A (Cortex-M4, 128 KB flash, 64 KB SRAM) |
| Flash @0x00400000 | SP `0x200011a8`, reset vector word `0x0040061d` | firmware vector table. Bit 0 of the reset entry marks Thumb state, so the handler is at `0x0040061c` |
| Registers | pc `0x0040061c`, sp `0x200011a8` | pc is the reset handler and sp the vector-table MSP, as expected after a reset halt |

The DPIDR, the CPUID core revision and the chip ID match the CW313 bit for bit, and the halt, flash and
register reads behave the same. The vector table, pc and sp depend on the firmware and differ from the
CW313 run only because I loaded a different build there. On the right-angle board the core halts at pc
`0x00400180` with sp `0x20001020`, and the SRAM and flash sections of that log are empty. So SWDIO (on
the TMS pin) and SWCLK (on the TCK pin) carry SWD end to end from the CW312 card edge to the UFO socket.

SWD leaves TDI and TDO unused. To exercise `JTAG_TDI` and `JTAG_TDO` I repeated the session in full JTAG
mode (`transport select jtag`) with wires 5 and 6 added. OpenOCD scanned the chain:

| Read over JTAG | Value | Meaning |
|---|---|---|
| TAP IDCODE | `0x4ba00477`, matches expected | ARM CoreSight JTAG-DP (`mfg: 0x23b (ARM Ltd), part: 0xba00, ver: 0x4`), captured in Capture-DR and shifted out on TDO |
| Core | `Cortex-M4 r0p1` | same core, from CPUID over JTAG |
| CHIPID_CIDR @0x400E0740 | `0x288b07e1` | chip ID, read over JTAG |

The IDCODE comes out on TDO, so it confirms `JTAG_TDO` (the MISO wire). The halt, chip ID, flash and pc
reads that follow shift their commands in on TDI and return data on TDO, so they also exercise `JTAG_TDI`
(the MOSI wire). The right-angle board gives the same IDCODE and reads. As expected, the TAP IDCODE
`0x4ba00477` differs from the SWD DPIDR `0x2ba01477`: they are the ID registers of the JTAG-DP and the
SW-DP, the two modes of the same CoreSight SWJ-DP debug port. Unlike the IEEE 1149.1 IDCODE, the SW-DP
DPIDR has a DP-version field in bits [15:12], and it encodes PARTNO in 8 bits against the IDCODE's 16.

Evidence: [`swd_cw313_dump.txt`](validation/evidence/swd_cw313_dump.txt),
[`swd_abductor_dump.txt`](validation/evidence/swd_abductor_dump.txt),
[`swd_abductor_ra_dump.txt`](validation/evidence/swd_abductor_ra_dump.txt),
[`jtag_cw313_dump.txt`](validation/evidence/jtag_cw313_dump.txt),
[`jtag_abductor_dump.txt`](validation/evidence/jtag_abductor_dump.txt) and
[`jtag_abductor_ra_dump.txt`](validation/evidence/jtag_abductor_ra_dump.txt). The straight-board SWD and
JTAG files are edited summaries of the OpenOCD output; the CW313 files are the raw logs.

### Signal coverage

Every pin the Abductor routes was exercised by a test, checked for continuity, or is marked as not
exercised in the matrix. The functional tests run small firmwares on the SAM4S.
[`signal_test.py`](validation/scripts/signal_test.py) flashes a test firmware and, for GPIO3, reads TIO3
back on the Husky Plus; the LED check is visual. The firmware sources are
[`led-blink/`](validation/scripts/firmware/led-blink/) and
[`abductor-sigtest/`](validation/scripts/firmware/abductor-sigtest/), built under the chipwhisperer
`firmware/mcu/` tree. The pin map comes from the CW312T-SAM4S schematic.

`led-blink.c` drives the three target LED lines in sequence, and the three UFO LEDs light one after the
other. `abductor-sigtest.c` drives GPIO3 (PA8) as a slow square wave, and TIO3 in `scope.io.tio_states`
follows it (seen at both 0 and 1). Both work on the right-angle board too. The target's `SJ1` jumper is
not on the GPIO3 path: it selects whether ERASE/PB12 follows PDIC (the default, which SAM-BA programming
needs) or GPIO3. The same firmware outputs PCK0 (MAINCK/8) on PA6, which is CLK_FROM_SAM, the target
clock-out. The Husky Plus frequency counter does not read the UFO clock-out path without extra
clock-routing setup, so I checked CLKOUT for continuity instead.

| Abductor signal | SAM4S pin | Checked by |
|---|---|---|
| VCC1.2 (core), FILTIN, VCC3.3 (IO), IOVREF, SHUNTH | power net | SCA and power capture |
| SHUNTL (the UFO SMA node) | power net | power capture, voltage glitch (high- and low-power crowbar) |
| FILT_HP, FILT_LP | core supply, one node on the UFO and on the CW312T-SAM4S | power capture; the two run in parallel, so neither is checked alone |
| CLKIN (HS2) | XIN / PB9 | SCA and clock glitch |
| GPIO1_TX / GPIO2_RX | PA10 / PA9 | serial (password bypass) |
| GPIO4 / trigger | PA7 | capture trigger |
| nRST, PDIC (ERASE) | RST / PB12 | SAM-BA programming |
| JTAG TMS / TCK / TDI / TDO | PB6 / PB7 / PB4 / PB5 | SWD and full JTAG |
| JTAG_VREF | debug net | not separable: the VREF wire feeds the same net |
| JTAG_nRST | debug net | not exercised (OpenOCD drove no reset) |
| LED1 / LED2 / LED3 | PA16 / PA15 / PA14 | led-blink firmware (visual) |
| GPIO3 | PA8 | sigtest firmware (TIO3 read-back) |
| CLKOUT (CLK_FROM_SAM) | PA6 (PCK0) | continuity, CW312 edge A29 to UFO CLKOUT (silkscreen CLKFB) |
| SCK, MOSI, PDID (CS) | not used by the SAM4S | iCE40 bitstream load |
| MISO | not used by the SAM4S | not exercised |
| VCC1.8 / 2.5 / 5.0 | power net | continuity (unused by the SAM4S) |
| HDR1-10, JTAG_TRST | passthrough | continuity |

The SAM4S does not use the extra VCC rails or HDR1-10, so those nets and CLKOUT got a continuity check
from the CW312 edge to the UFO breakout. Every checked net was continuous.

The parallel ETM trace pins (TRACECLK, TRACED0-3) cannot be tested on this setup: the ATSAM4S2A has no
ETM (NewAE's "Husky TraceWhisperer Exploration" demo says it cannot be used with the SAM4S for that
reason). The CW312T-SAM4S schematic leaves those pins unconnected at the card edge, the Abductor leaves
them unrouted at its socket, and the UFO schematic, a 2016 design, has no trace pins either. SWO, the
SAM4S single-wire trace output, shares the `TDO/TRACESWO` pin, which the full JTAG test exercises as
`JTAG_TDO`.

## CW312T-iCE40UP FPGA

The CW312T-iCE40UP (a Lattice iCE40 UltraPlus iCE40UP5K FPGA, about 5280 LUTs, 30-ball WLCSP) is a
different class of target. Through the Abductor it gave the same attack outcomes as on the CW313, with
slightly different raw leakage metrics. It runs a hardware AES core in the FPGA fabric, is configured
with a bitstream over SPI, talks over the SimpleSerial v2 (SS2) wrapper, and leaks on the last AES round.
The repository has the CW313 convergence, TVLA and DFA results.

Take the SAM4S debug wires off the UFO `J8` header first ([Using the board](#using-the-board)). No iCE40
test needs them.

### Bring-up

The `iCE40UP5K_SS2` AES bitstream loads and the FPGA configures, so the Abductor routes the configuration
path: SCK, MOSI, the chip select on PDID and the reset on nRST. The loader only writes, and it does not
read CDONE on PDIC, so this target does not exercise MISO or PDIC. A known-answer test passes,
`AES(0,0) = 66e94bd4ef8a2c3b884cfa59ca342b2e`, so the SS2 serial and the clock reach the FPGA and the
core runs. Both steps pass on the right-angle board too.

### CPA and TVLA

[`ice40_hw_aes_cpa.py`](validation/scripts/ice40_hw_aes_cpa.py) runs CPA over 5000 traces with the
last-round Hamming-distance (HD) model, `cwa.leakage_models.last_round_state_diff`: the Hamming distance
between the round-9 and round-10 state-register values, valid for this round-based core that does one
round per cycle. It recovers the round-10 key, and the inverse key schedule gives the master key, 16/16
bytes correct (`2b7e151628aed2a6abf7158809cf4f3c`), on the right-angle board too.

That takes thousands of traces, against 30 for the SAM4S software AES. The FPGA core completes a full
round in one clock cycle with all 16 S-boxes switching at once. So the other 15 bytes add algorithmic
noise, and the SNR of any single byte is far lower than in the software AES, whose S-box lookups run in
turn over many cycles. The hardware AES still leaks overall, as the TVLA shows.

[`ice40_sca_metrics.py`](validation/scripts/ice40_sca_metrics.py) measures two metrics:

- CPA convergence with the same model reaches the full key by 3000 traces, the next grid point after 2000
  (8/16 bytes at 700 traces, 15/16 at 2000). The 5000 traces of the CPA run are a safety margin.
- A non-specific TVLA (about 2000 + 2000 traces) gives max |t| = 85.0 against the 4.5 threshold, a
  first-order leak through the Abductor's power path.

Plots: [`ice40_cpa_convergence.png`](validation/img/ice40_cpa_convergence.png) and
[`ice40_tvla.png`](validation/img/ice40_tvla.png). On the CW313 the full key also falls by 3000 traces
(14/16 at 2000) and TVLA gives max |t| = 89.3 against 85.0, so the two paths were close
([`cw313/ice40_cpa_convergence.png`](validation/img/cw313/ice40_cpa_convergence.png),
[`cw313/ice40_tvla.png`](validation/img/cw313/ice40_tvla.png)).

On the right-angle board the first convergence run needed 5000 traces for the last, weakest key byte, and
a repeat reached the full key by 3000 like the straight board. That is most likely run-to-run variation
on the weakest byte of a parallel hardware AES, but one repeat cannot rule out an effect of the
right-angle board. Its TVLA gives max |t| = 85.8. The right-angle figures are under `validation/img/ra/`.

### Fault attack (DFA)

A clock glitch on HS2, the FPGA's clock, faults the AES core, and a differential fault attack (DFA) on
those faults recovers the full key on all three setups. The attack follows the official ChipWhisperer DFA
lab (`fault201 Lab 1_3B - DFA Attack on AES`) and uses the same cracker, `phoenixAES` (Philippe Teuwen's
tool, in the JeanGrey repository of the SideChannelMarvels project).

Before the glitch campaign, [`dfa_selftest.py`](validation/scripts/dfa_selftest.py) checks both fault
models offline. Its software AES gives `AES(0,0) = 66e94bd4...` (asserted) and
`AES(2b7e..,00..0f) = 50fe67cc996d32b6da0937e99bafec60`, printed next to the value the FPGA returned on
the bench. It then recovers the key from simulated round-9 and round-8 faults.

A round-9 fault (Piret and Quisquater) is a single-byte fault just before the last MixColumns, and it
gives a 4-byte diagonal ciphertext difference (for example bytes 0/7/10/13). This works, but the FPGA
runs a parallel AES, so a fixed plaintext faults only one data-dependent diagonal. Getting all four
diagonals this way was impractical here: one diagonal was very rare across the plaintexts I tried, though
more plaintexts might bring it out.

A single-byte fault one round earlier, in round 8, diffuses fully. `phoenixAES.convert_r8faults_bytes`
turns one such output into round-9 faults on all four diagonals at once, so a few clean round-8 faults
are enough in principle. On hardware, [`ice40_dfa_phoenix.py`](validation/scripts/ice40_dfa_phoenix.py)
keeps every output with 14 or more changed bytes as a round-8 candidate (129 for the known-answer
plaintext on the straight board), and it also keeps the clean round-9 faults. It merges what phoenixAES
cracks from both into one key. On the straight board the known-answer plaintext gave 12 of 16 round-10
key bytes (diagonals 0, 1 and 2) and a second plaintext gave the last diagonal. On the right-angle board
and the CW313 the known-answer plaintext gave all 16.

The recovered round-10 key is `d014f9a8c9ee2589e13f0cc8b6630ca6`. Inverting the key schedule
(`aes_funcs.key_schedule_rounds(r10, 10, 0)`) gives the master key `2b7e151628aed2a6abf7158809cf4f3c`,
16/16 bytes correct. The script writes the evidence:
[`ice40_dfa_abductor.txt`](validation/evidence/ice40_dfa_abductor.txt),
[`ice40_dfa_ra.txt`](validation/evidence/ice40_dfa_ra.txt) and
[`ice40_dfa_cw313.txt`](validation/evidence/ice40_dfa_cw313.txt). Each file lists the first six round-8
candidates per plaintext. None of those is a clean single-byte round-8 fault: checked against the known
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
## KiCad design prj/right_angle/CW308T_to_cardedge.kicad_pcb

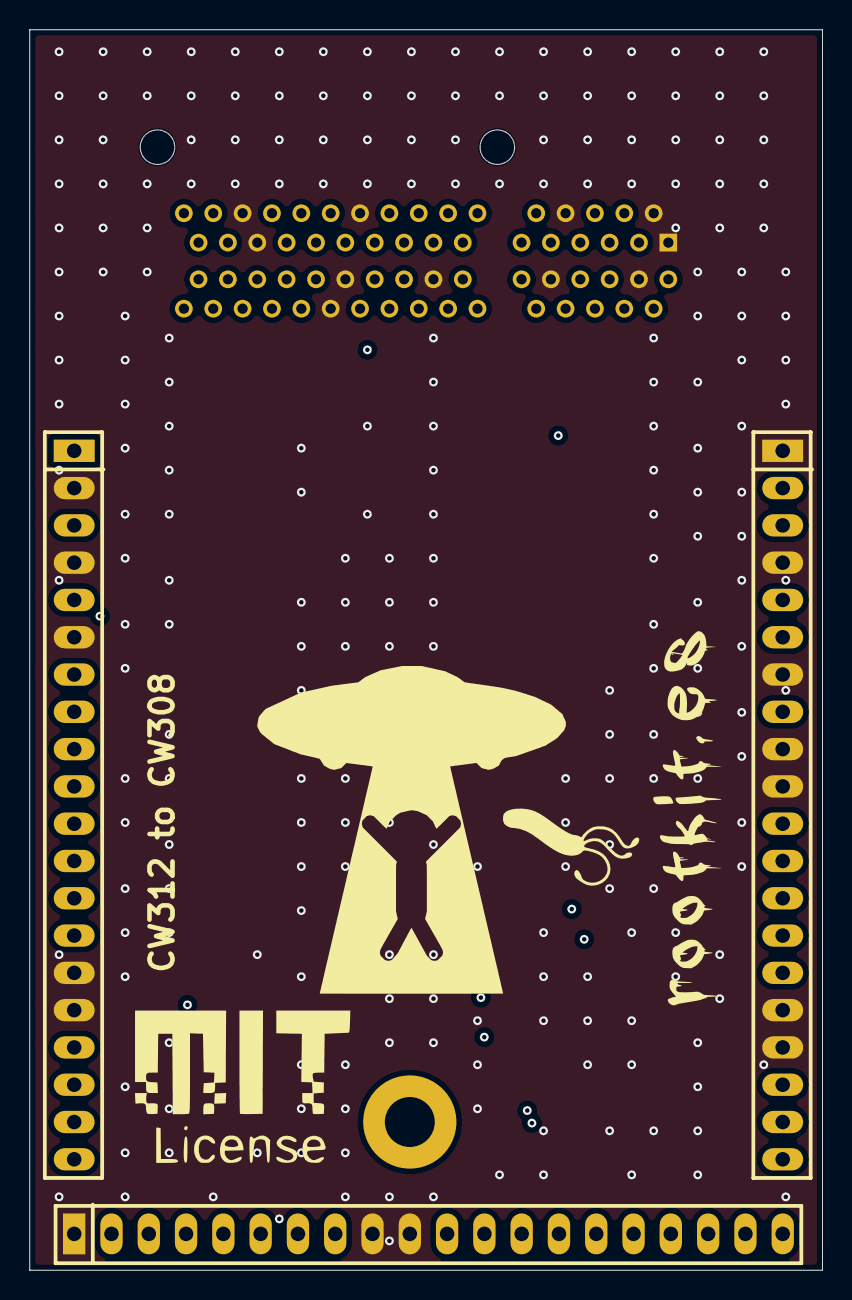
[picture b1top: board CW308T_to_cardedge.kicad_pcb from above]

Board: 6 copper layers, 54.0 x 84.5 mm, 6 parts (1 on the bottom side), 44 nets.

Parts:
CN1: PCIE-064-02-F-D-RA; CONN-TH_64P-P1.00_PCIE-064-02-F-D-RA
G6566, G34434, G344333, G565656: LOGO
J1: CW308_TARGETCON; CW308_TBOARD_CONN

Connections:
/CLKIN: CN1.A29, J1.A5 (CLKIN(FROM_TARGET))
/CLKOUT: CN1.B27, J1.A3 (CLKOUT(TO_TARGET))
/FILTIN: CN1.B5, J1.C8 (FILTIN)
/FILT_HP: CN1.B4, J1.C6 (FILT_HP)
/FILT_LP: CN1.A3, J1.C5 (FILT_LP)
/GPIO1/TX: CN1.B16, J1.A7 (GPIO1)
/GPIO2/RX: CN1.B17, J1.A8 (GPIO2)
/GPIO3: CN1.B18, J1.A9 (GPIO3)
/GPIO4/TRIG: CN1.B19, J1.A10 (GPIO4)
/HDR1: CN1.A9, J1.B11 (HDR1)
/HDR2: CN1.A10, J1.B12 (HDR2)
/HDR3: CN1.A11, J1.B13 (HDR3)
/HDR4: CN1.A12, J1.B14 (HDR4)
/HDR5: CN1.A13, J1.B15 (HDR5)
/HDR6: CN1.A14, J1.B16 (HDR6)
/HDR7: CN1.A15, J1.B17 (HDR7)
/HDR8: CN1.A16, J1.B18 (HDR8)
/HDR9: CN1.A17, J1.B19 (HDR9)
/HDR10: CN1.A18, J1.B20 (HDR10)
/IOVREF: CN1.B10, J1.A20 (VREF)
/JTAG_TCK: CN1.B32, J1.B6 (JTAG_TCK)
/JTAG_TDI: CN1.B29, J1.B3 (JTAG_TDI)
/JTAG_TDO: CN1.B30, J1.B4 (JTAG_TDO)
/JTAG_TMS: CN1.B31, J1.B5 (JTAG_TMS)
/JTAG_TRST: CN1.A32, J1.B2 (JTAG_TRST)
/JTAG_VREF: CN1.A26, J1.B7 (JTAG_VREF)
/JTAG_nRST: CN1.A31, J1.B8 (JTAG_nRST)
/LED1: CN1.B11, J1.C18 (LED1)
/LED2: CN1.B12, J1.C19 (LED2)
/LED3: CN1.B13, J1.C20 (LED3)
/MISO: CN1.B23, J1.A13 (MISO)
/MOSI: CN1.B24, J1.A14 (MOSI)
/PDIC: CN1.B25, J1.A17 (PDIC)
/PDID: CN1.B26, J1.A18 (PDID)
/SCK: CN1.B20, J1.A12 (SCK)
/SHUNTH: CN1.B2, J1.C3 (SHUNTH)
/SHUNTL: CN1.B1, J1.C2 (SHUNTL)
/VCC1.2: CN1.B7, J1.C11 (VCC1.2V)
/VCC1.8: CN1.B8, J1.C12 (VCC1.8V)
/VCC2.5: CN1.A4, J1.C13 (VCC2.5V)
/VCC3.3: CN1.A5, J1.C14 (VCC3.3V)
/VCC5.0: CN1.A6, J1.C15 (VCC5.0V)
/nRST: CN1.B14, J1.A11 (nRST)
GND: CN1.A1, CN1.A2, CN1.A8, CN1.A20, CN1.A27, CN1.A28, CN1.B3, CN1.B9, CN1.B15, CN1.B21, CN1.B22, J1.A2 (GND), J1.A4 (GND), J1.A6 (GND), J1.A15 (GND), J1.A16 (GND), J1.B1 (GND), J1.B9 (GND), J1.B10 (GND), J1.C1 (GND), J1.C4 (GND), J1.C7 (GND), J1.C9 (GND), J1.C10 (GND), J1.C16 (GND), J1.C17 (GND)

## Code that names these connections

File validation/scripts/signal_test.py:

#!/usr/bin/env python3
# MIT License
#
# Copyright (c) 2026 David Reguera Garcia (aka Dreg)
# dreg@rootkit.es - https://github.com/therealdreg/abductor
#
# Disclaimer: this is the work of a hobbyist, shared in good faith for educational
# purposes. It is not professional work and may contain mistakes or inaccuracies;
# corrections and feedback are welcome. Provided "as is" and used at your own risk.
#
# Permission is hereby granted, free of charge, to any person obtaining a copy
# of this software and associated documentation files (the "Software"), to deal
# in the Software without restriction, including without limitation the rights
# to use, copy, modify, merge, publish, distribute, sublicense, and/or sell
# copies of the Software, and to permit persons to whom the Software is
# furnished to do so, subject to the following conditions:
#
# The above copyright notice and this permission notice shall be included in all
# copies or substantial portions of the Software.
#
# THE SOFTWARE IS PROVIDED "AS IS", WITHOUT WARRANTY OF ANY KIND, EXPRESS OR
# IMPLIED, INCLUDING BUT NOT LIMITED TO THE WARRANTIES OF MERCHANTABILITY,
# FITNESS FOR A PARTICULAR PURPOSE AND NONINFRINGEMENT. IN NO EVENT SHALL THE
# AUTHORS OR COPYRIGHT HOLDERS BE LIABLE FOR ANY CLAIM, DAMAGES OR OTHER
# LIABILITY, WHETHER IN AN ACTION OF CONTRACT, TORT OR OTHERWISE, ARISING FROM,
# OUT OF OR IN CONNECTION WITH THE SOFTWARE OR THE USE OR OTHER DEALINGS IN THE
# SOFTWARE.

"""
Abductor signal test on the CW312T-SAM4S with a ChipWhisperer Husky Plus: flash a test firmware
over SAM-BA, then check the signal it drives. It runs the same way on the straight board, the
right-angle board and the CW313.

The firmware sources and makefiles are in firmware/ next to this script. Their makefiles include
files from the chipwhisperer firmware tree, so copy each folder into chipwhisperer/firmware/mcu/
and build it there:
    cd firmware/mcu/led-blink       && make PLATFORM=CW312_SAM4S CRYPTO_TARGET=NONE SS_VER=SS_VER_2_1
    cd firmware/mcu/abductor-sigtest && make PLATFORM=CW312_SAM4S CRYPTO_TARGET=NONE SS_VER=SS_VER_2_1
Each build writes led-blink-CW312_SAM4S.hex or abductor-sigtest-CW312_SAM4S.hex in its folder.

Usage (the hex path is required; the mode defaults to gpio3):
    signal_test.py <firmware.hex> led     # led-blink: watch LED1/2/3 (PA16/PA15/PA14) blink in turn
    signal_test.py <firmware.hex> gpio3   # abductor-sigtest: read GPIO3 (PA8) back as TIO3

led only flashes the firmware and waits 6 s while you watch the LEDs. gpio3 reads TIO3 16 times,
0.35 s apart: seeing both 0 and 1 shows that GPIO3 is routed to TIO3. Results go to the console.

Pin map (from the CW312T-SAM4S schematic): LED1=PA16, LED2=PA15, LED3=PA14, GPIO3=PA8,
CLKOUT/CLK_FROM_SAM=PA6 (PCK0), trigger/GPIO4=PA7, UART=PA9/PA10, CLKIN=XIN/PB9.
"""
import sys, time
import chipwhisperer as cw

HEX  = sys.argv[1]
MODE = sys.argv[2] if len(sys.argv) > 2 else 'gpio3'

scope = cw.scope(); scope.default_setup()
# Up to 3 programming tries, 1 s apart; if all fail, the script stops with exit status 2.
for k in range(3):
    try:
        cw.program_target(scope, cw.programmers.SAM4SProgrammer, HEX); print('FLASHED'); break
    except Exception as e:
        print('flash retry:', str(e)[:60]); time.sleep(1.0)
else:
    print('!!! SAM-BA programming failed after retries. Please reconnect the Husky USB.'); scope.dis(); raise SystemExit(2)
# Pulse nRST low for 50 ms, release it and give the firmware 300 ms to start.
scope.io.nrst = 'low'; time.sleep(0.05); scope.io.nrst = 'high_z'; time.sleep(0.3)

if MODE == 'gpio3':
    # TIO3 as a high-Z input, so it only follows what the target drives on GPIO3.
    scope.io.tio3 = 'high_z'; seen = set()
    for i in range(16):
        # tio_states is (TIO1, TIO2, TIO3, TIO4), so st[2] is TIO3.
        st = scope.io.tio_states; seen.add(int(st[2]))
        print('t=%4.1fs  TIO(1,2,3,4)=%s' % (i * 0.35, st)); time.sleep(0.35)
    # SJ1 is not on the GPIO3 path: it only selects whether ERASE/PB12 follows PDIC (the default,
    # which SAM-BA programming needs) or GPIO3, so a stuck TIO3 points at the GPIO3 routing.
    print('=> GPIO3/TIO3 seen', sorted(seen), '->',
          'TOGGLES = ROUTED OK' if len(seen) > 1 else 'STUCK (check the GPIO3 routing)')
elif MODE == 'led':
    # Nothing to read back: the LED check is visual.
    print('Watch the CW308 target LEDs: LED1(PA16) -> LED2(PA15) -> LED3(PA14) in sequence.')
    time.sleep(6)

scope.dis()

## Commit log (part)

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2026-06-29 first version
